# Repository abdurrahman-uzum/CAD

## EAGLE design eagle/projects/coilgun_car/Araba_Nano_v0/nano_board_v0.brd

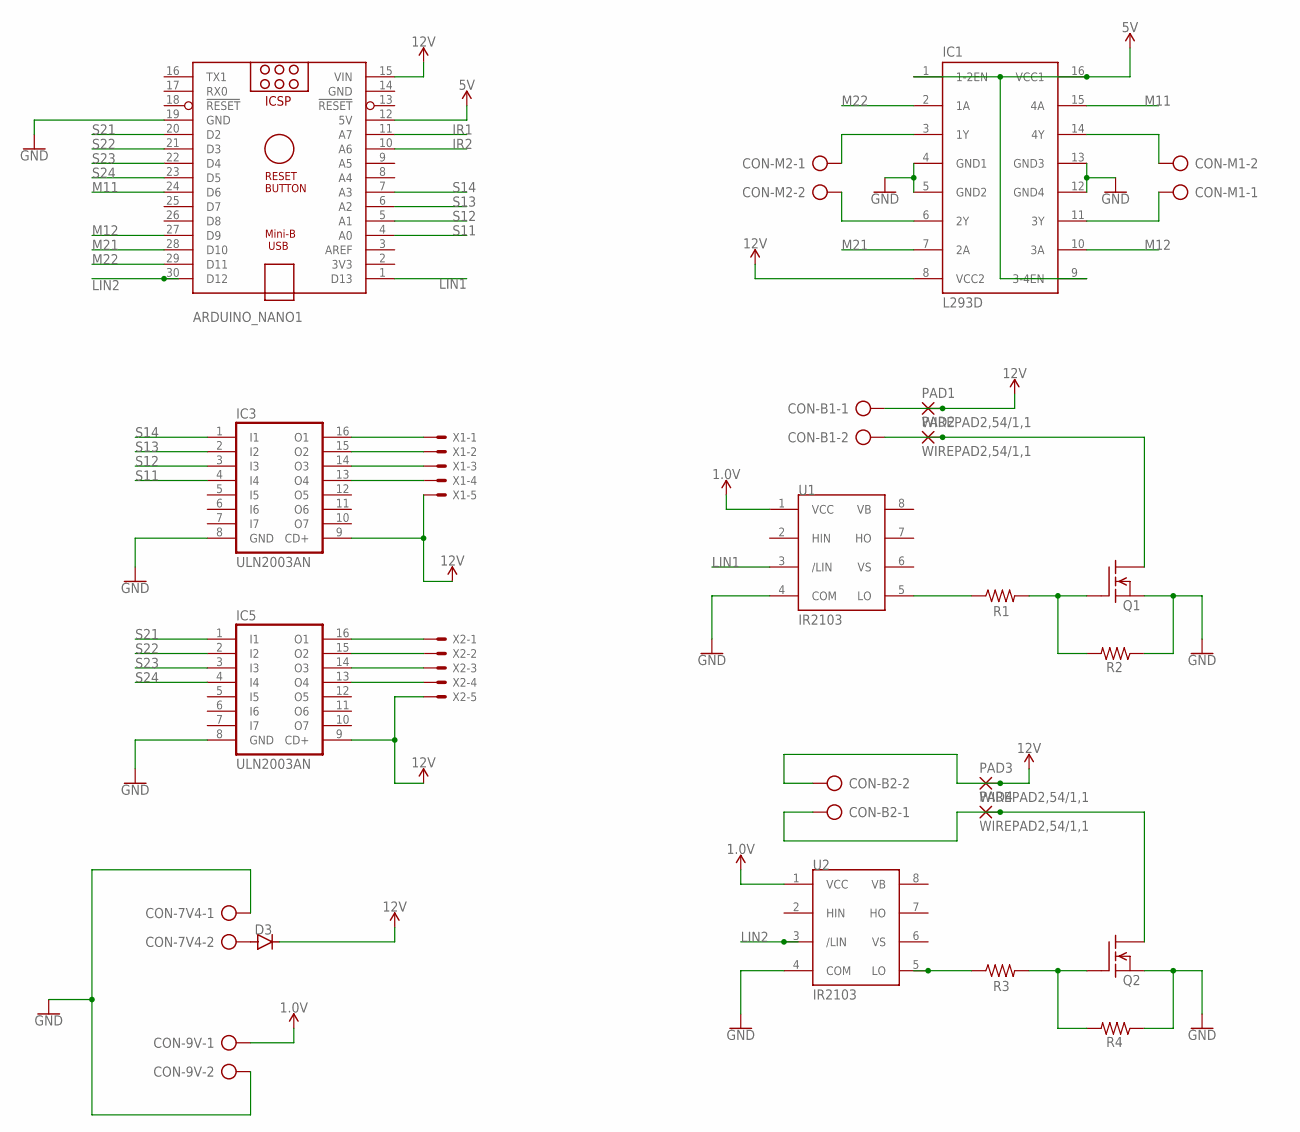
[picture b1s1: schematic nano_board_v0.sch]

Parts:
ARDUINO_NANO1: ARDUINO_NANO
CON-7V4, CON-9V: AK500/2
CON-B1, CON-B2: AK500/2
CON-M1, CON-M2: AK500/2
D3: 1N4004; DO41-10
IC1: L293D; DIL16
IC3, IC5: ULN2003AN; DIL16
PAD1, PAD2, PAD3, PAD4: WIREPAD2,54/1,1; 2,54/1,1
Q1, Q2: IRF510; TO220
R1, R2, R3, R4: R-US_0204/7; 0204/7
U1, U2: IR2103; DIL08
X1, X2: JST-XH-05-PIN-LONG-PAD; JST-XH-05-PACKAGE-LONG-PAD

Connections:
1.0V: CON-9V.1, U1.1 (VCC), U2.1 (VCC)
5V: ARDUINO_NANO1.12 (5V), IC1.1 (1-2EN), IC1.9 (3-4EN), IC1.16 (VCC1)
12V: ARDUINO_NANO1.15 (VIN), CON-B1.1, CON-B2.2, D3.C, IC1.8 (VCC2), IC3.9 (CD+), IC5.9 (CD+), PAD1.1, PAD3.1, X1.5, X2.5
GND: ARDUINO_NANO1.14 (GND), ARDUINO_NANO1.19 (GND), CON-7V4.1, CON-9V.2, IC1.4 (GND1), IC1.5 (GND2), IC1.12 (GND4), IC1.13 (GND3), IC3.8 (GND), IC5.8 (GND), Q1.3 (S), Q2.3 (S), R2.1, R4.1, U1.4 (COM), U2.4 (COM)
IR1: ARDUINO_NANO1.11 (A7)
IR2: ARDUINO_NANO1.10 (A6)
LIN1: ARDUINO_NANO1.1 (D13), U1.3 (/LIN)
LIN2: ARDUINO_NANO1.30 (D12), U2.3 (/LIN)
M11: ARDUINO_NANO1.24 (D6), IC1.15 (4A)
M12: ARDUINO_NANO1.27 (D9), IC1.10 (3A)
M21: ARDUINO_NANO1.28 (D10), IC1.7 (2A)
M22: ARDUINO_NANO1.29 (D11), IC1.2 (1A)
unnamed: R1.1, U1.5 (LO)
unnamed: Q1.1 (G), R1.2, R2.2
unnamed: R3.1, U2.5 (LO)
unnamed: IC3.16 (O1), X1.1
unnamed: IC3.15 (O2), X1.2
unnamed: CON-M1.2, IC1.14 (4Y)
unnamed: CON-M1.1, IC1.11 (3Y)
unnamed: CON-M2.1, IC1.3 (1Y)
unnamed: CON-M2.2, IC1.6 (2Y)
unnamed: CON-B1.2, PAD2.1, Q1.2 (D)
unnamed: Q2.1 (G), R3.2, R4.2
unnamed: IC3.14 (O3), X1.3
unnamed: IC3.13 (O4), X1.4
unnamed: IC5.16 (O1), X2.1
unnamed: IC5.15 (O2), X2.2
unnamed: CON-B2.1, PAD4.1, Q2.2 (D)
unnamed: CON-7V4.2, D3.A
unnamed: IC5.14 (O3), X2.3
unnamed: IC5.13 (O4), X2.4
S11: ARDUINO_NANO1.4 (A0), IC3.4 (I4)
S12: ARDUINO_NANO1.5 (A1), IC3.3 (I3)
S13: ARDUINO_NANO1.6 (A2), IC3.2 (I2)
S14: ARDUINO_NANO1.7 (A3), IC3.1 (I1)
S21: ARDUINO_NANO1.20 (D2), IC5.1 (I1)
S22: ARDUINO_NANO1.21 (D3), IC5.2 (I2)
S23: ARDUINO_NANO1.22 (D4), IC5.3 (I3)
S24: ARDUINO_NANO1.23 (D5), IC5.4 (I4)

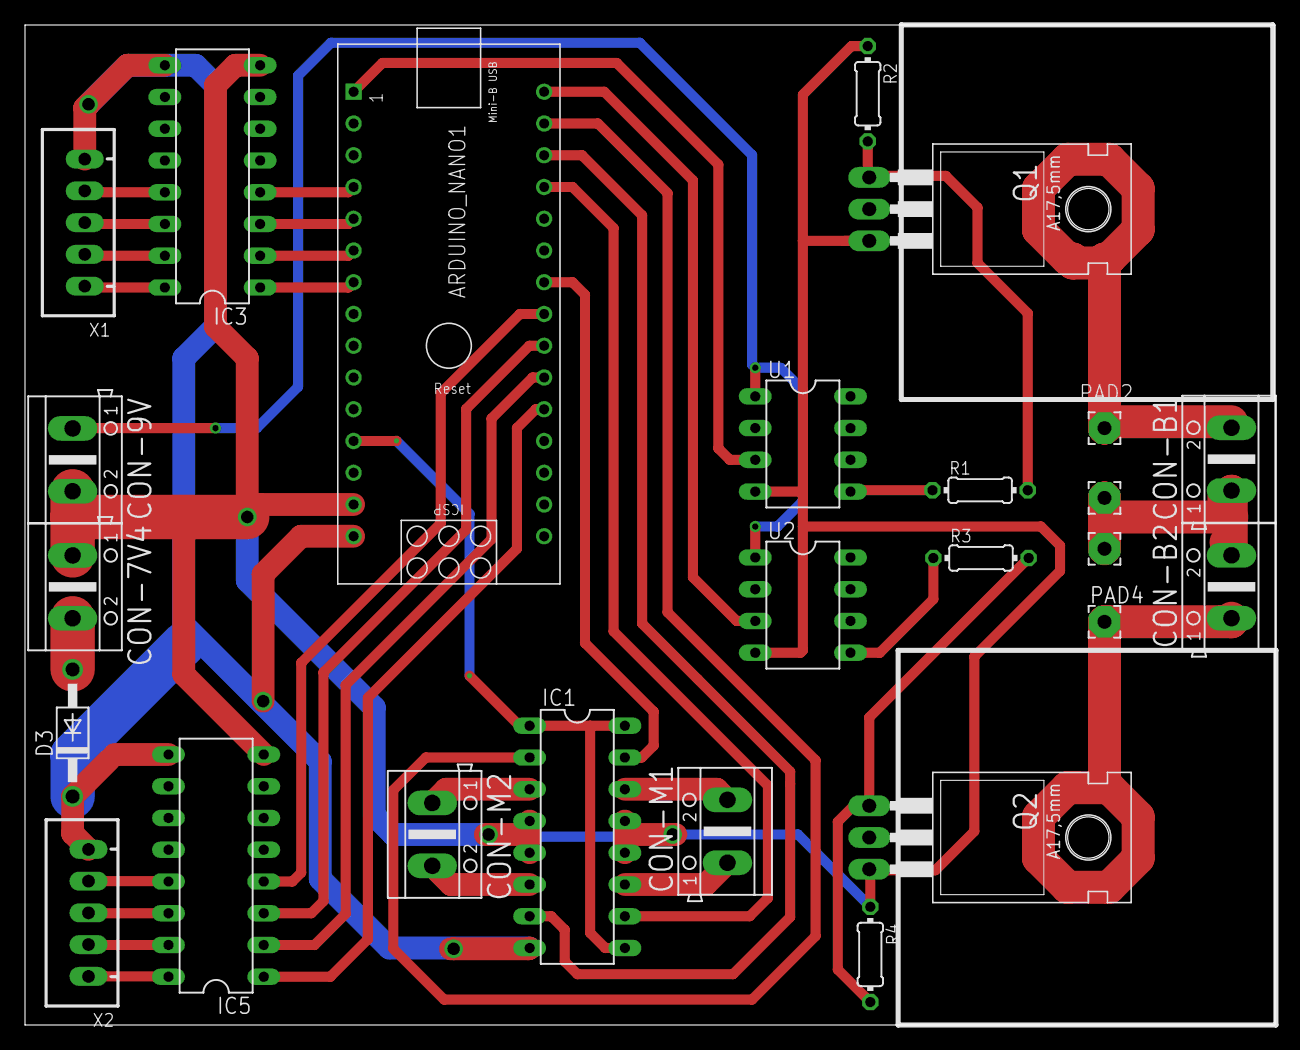
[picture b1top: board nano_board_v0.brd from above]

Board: 2 copper layers, 100.0 x 80.0 mm, 25 parts (0 on the bottom side), 37 nets.

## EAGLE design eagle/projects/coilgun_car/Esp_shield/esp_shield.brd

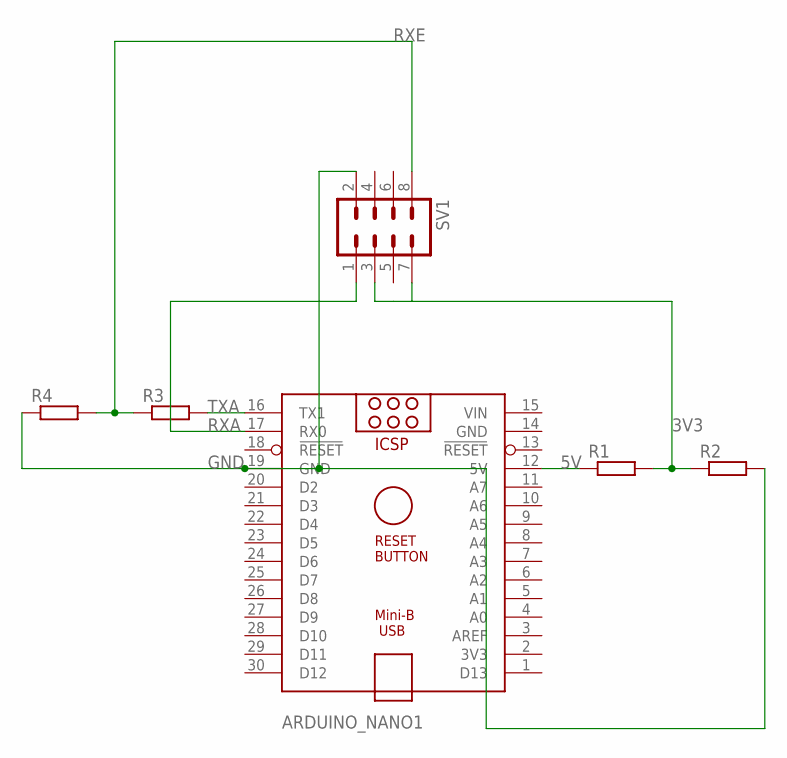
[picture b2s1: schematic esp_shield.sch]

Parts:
ARDUINO_NANO1: ARDUINO_NANO
R1, R2, R3, R4: R-EU_0204/7; 0204/7
SV1: MA04-2

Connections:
3V3: R1.2, R2.1, SV1.3, SV1.7
5V: ARDUINO_NANO1.12 (5V), R1.1
GND: ARDUINO_NANO1.14 (GND), ARDUINO_NANO1.19 (GND), R2.2, R4.1, SV1.2
RXA: ARDUINO_NANO1.17 (RX0), SV1.1
RXE: R3.1, R4.2, SV1.8
TXA: ARDUINO_NANO1.16 (TX1), R3.2
VIN: ARDUINO_NANO1.15 (VIN)

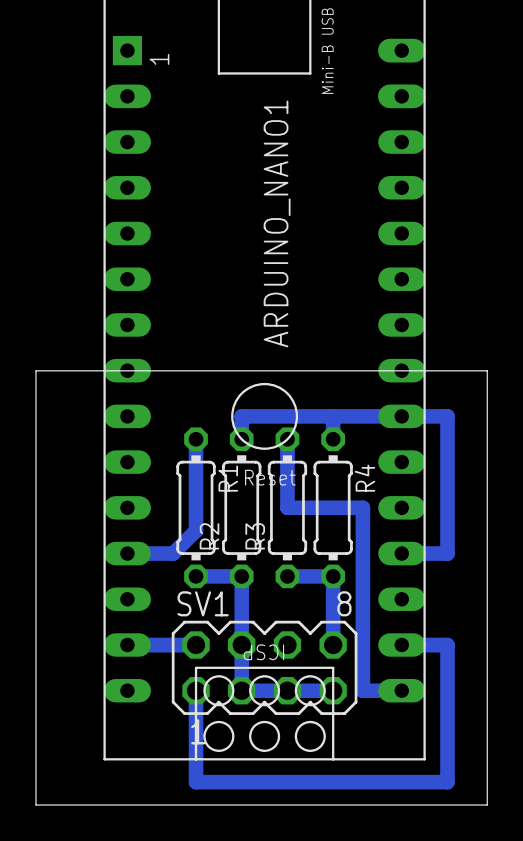
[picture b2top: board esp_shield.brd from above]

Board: 2 copper layers, 25.1 x 24.1 mm, 6 parts (0 on the bottom side), 6 nets.

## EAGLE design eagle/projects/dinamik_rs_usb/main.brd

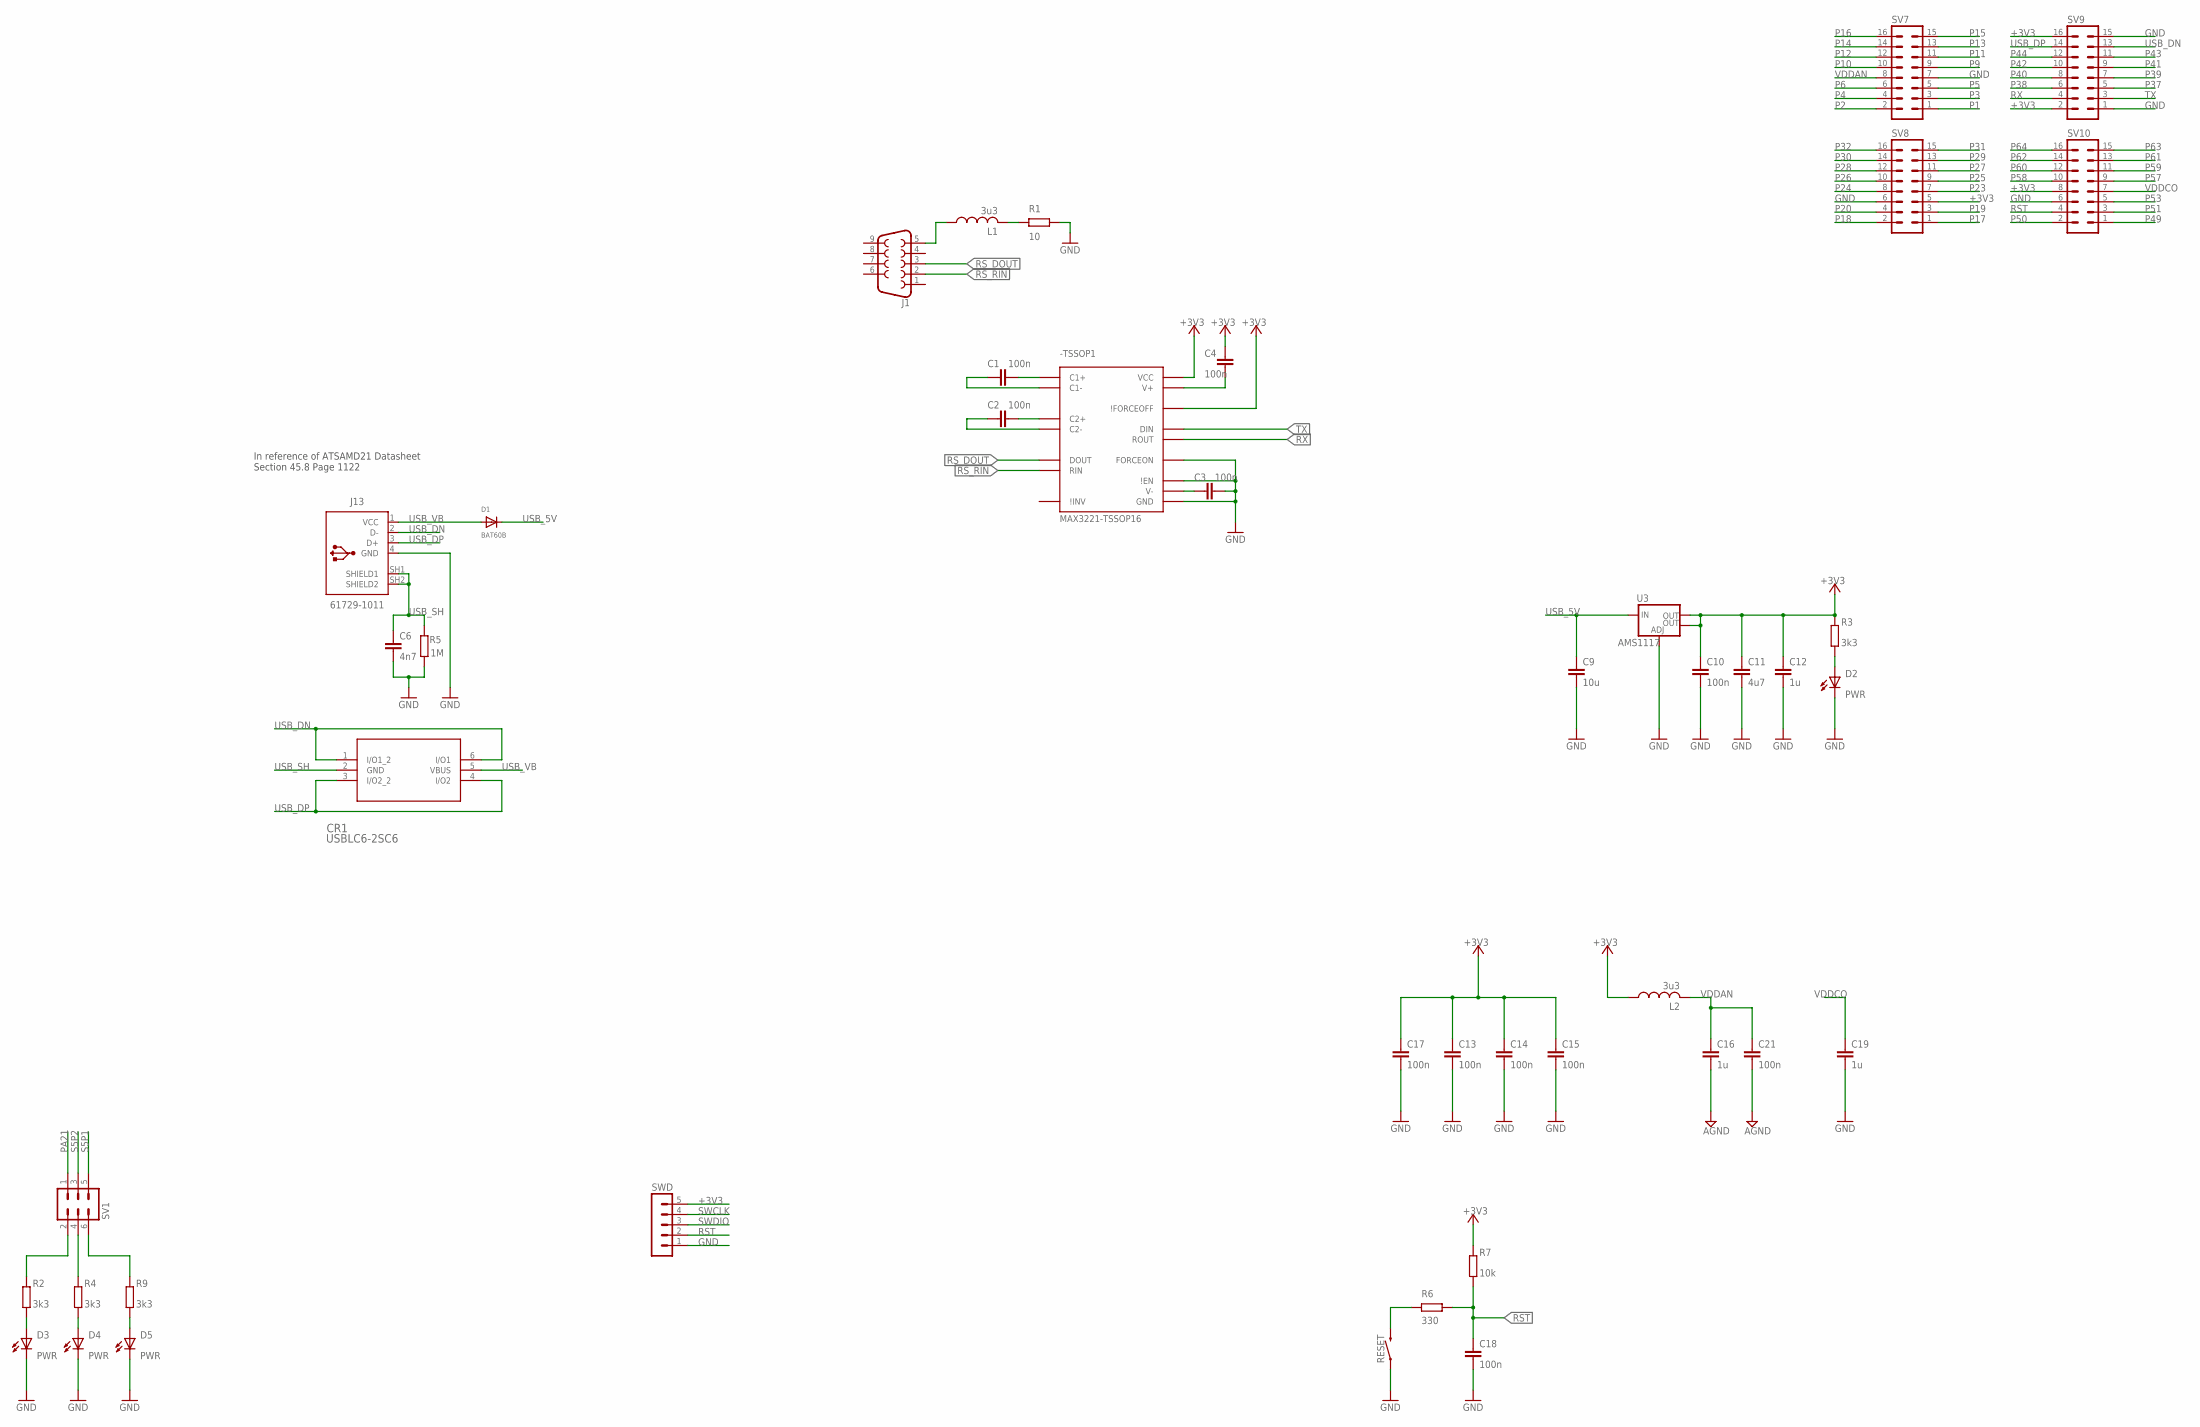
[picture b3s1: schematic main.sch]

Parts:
-TSSOP1: MAX3221-TSSOP16; TSSOP16
C1, C2, C3, C4, C10, C13, C14, C15, C17, C18, C21: 100n; C0603
C6: 4n7; C0603
C9: 10u; C0603
C11: 4u7; C0603
C12, C16, C19: 1u; C0603
CR1: USBLC6-2SC6; SOT23-6L_STM
D1: BAT60B; SOD-323F
D2, D3, D4, D5: PWR; CHIPLED_0805
J1: DB9FEMALE; DB9
J13: 61729-1011; 61729-1011BLF
L1, L2: 3u3; L3216C
R1: 10; R0603
R2, R3, R4, R9: 3k3; R0603
R5: 1M; R0603
R6: 330; R0603
R7: 10k; R0603
RESET: MOMENTARY-SWITCH-SPST-SMD-6.0X3.5MM; TACTILE_SWITCH_SMD_6.0X3.5MM
SV1: MA03-2
SV7, SV8, SV9, SV10: MA08-2
SWD: MA05-1
U3: AMS1117; SOT223

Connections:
+3V3: -TSSOP1.15 (VCC), -TSSOP1.16 (\!FORCEOFF), C4.2, C10.1, C11.1, C12.1, C13.1, C14.1, C15.1, C17.1, L2.1, R3.2, R7.1, SV8.5, SV9.2, SV9.16, SV10.8, SWD.5, U3.2 (OUT), U3.4 (OUT)
GND: -TSSOP1.1 (\!EN), -TSSOP1.12 (FORCEON), -TSSOP1.14 (GND), C3.2, C6.2, C9.2, C10.2, C11.2, C12.2, C13.2, C14.2, C15.2, C16.2, C17.2, C18.2, C19.2, C21.2, D2.C, D3.C, D4.C, D5.C, J13.4 (GND), R1.2, R5.2, RESET.1, SV7.7, SV8.6, SV9.1, SV9.15, SV10.6, SWD.1, U3.1 (ADJ)
unnamed: -TSSOP1.4 (C1-), C1.1
unnamed: R6.1, RESET.2
unnamed: -TSSOP1.7 (V-), C3.1
unnamed: D2.A, R3.1
unnamed: D3.A, R2.1
unnamed: D4.A, R4.1
unnamed: -TSSOP1.6 (C2-), C2.1
unnamed: J1.5, L1.1
unnamed: D5.A, R9.1
unnamed: R2.2, SV1.2
unnamed: R4.2, SV1.4
unnamed: R9.2, SV1.6
unnamed: -TSSOP1.3 (V+), C4.1
unnamed: L1.2, R1.1
unnamed: -TSSOP1.2 (C1+), C1.2
unnamed: -TSSOP1.5 (C2+), C2.2
P1: SV7.1
P2: SV7.2
P3: SV7.3
P4: SV7.4
P5: SV7.5
P6: SV7.6
P9: SV7.9
P10: SV7.10
P11: SV7.11
P12: SV7.12
P13: SV7.13
P14: SV7.14
P15: SV7.15
P16: SV7.16
P17: SV8.1
P18: SV8.2
P19: SV8.3
P20: SV8.4
P23: SV8.7
P24: SV8.8
P25: SV8.9
P26: SV8.10
P27: SV8.11
P28: SV8.12
P29: SV8.13
P30: SV8.14
P31: SV8.15
P32: SV8.16
P37: SV9.5
P38: SV9.6
P39: SV9.7
P40: SV9.8
P41: SV9.9
P42: SV9.10
P43: SV9.11
P44: SV9.12
P49: SV10.1
P50: SV10.2
P51: SV10.3
P53: SV10.5
P57: SV10.9
P58: SV10.10
P59: SV10.11
P60: SV10.12
P61: SV10.13
P62: SV10.14
P63: SV10.15
P64: SV10.16
PA21: SV1.1
RST: C18.1, R6.2, R7.2, SV10.4, SWD.2
RS_DOUT: -TSSOP1.13 (DOUT), J1.3
RS_RIN: -TSSOP1.8 (RIN), J1.2
RX: -TSSOP1.9 (ROUT), SV9.4
S5P1: SV1.5
S5P2: SV1.3
SWCLK: SWD.4
SWDIO: SWD.3
TX: -TSSOP1.11 (DIN), SV9.3
USB_5V: C9.1, D1.C, U3.3 (IN)
USB_DN: CR1.1 (I/O1_2), CR1.6 (I/O1), J13.2 (D-), SV9.13
USB_DP: CR1.3 (I/O2_2), CR1.4 (I/O2), J13.3 (D+), SV9.14
USB_SH: C6.1, CR1.2 (GND), J13.SH1 (SHIELD1), J13.SH2 (SHIELD2), R5.1
USB_VB: CR1.5 (VBUS), D1.A, J13.1 (VCC)
VDDAN: C16.1, C21.1, L2.2, SV7.8
VDDCO: C19.1, SV10.7

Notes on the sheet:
In reference of ATSAMD21 Datasheet Section 45.8 Page 1122

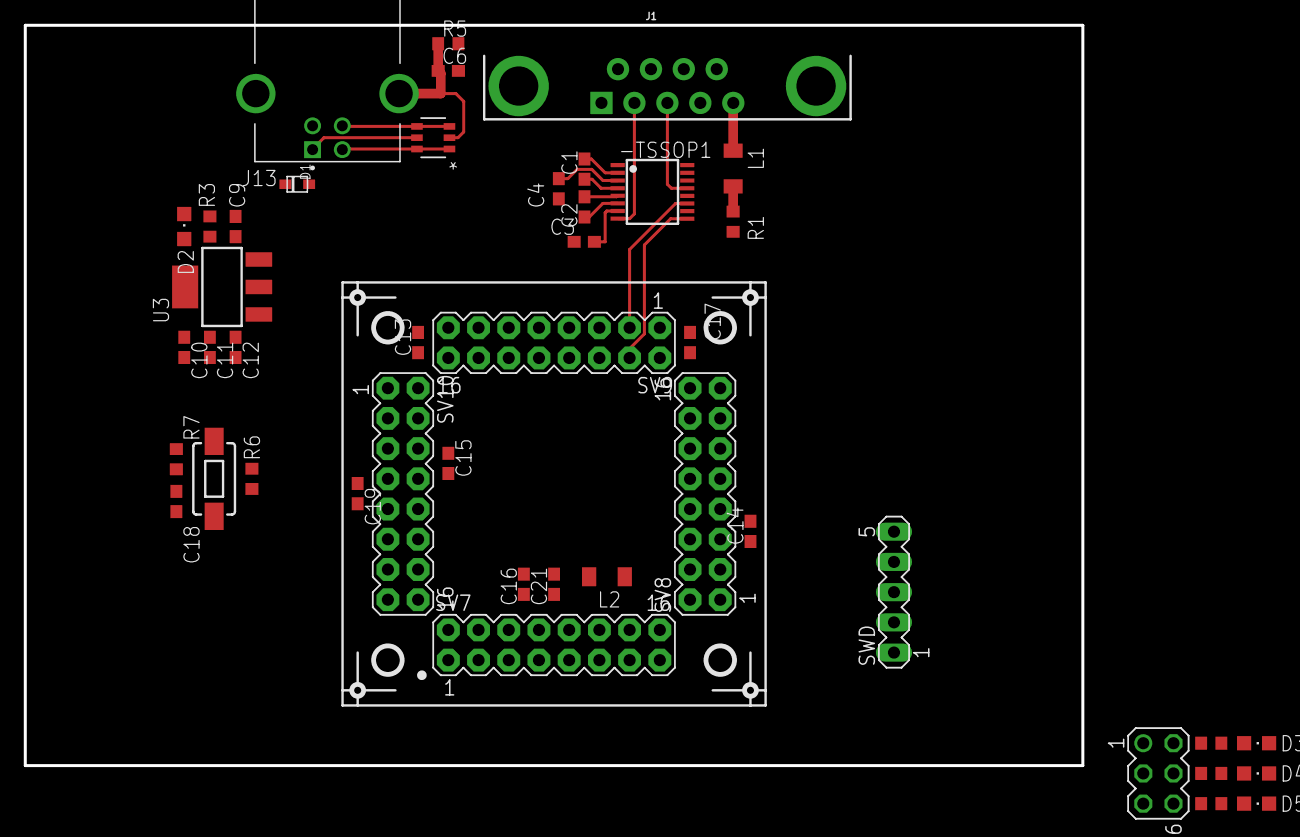
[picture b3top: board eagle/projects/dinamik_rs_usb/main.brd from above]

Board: 2 copper layers, 88.9 x 62.2 mm, 44 parts (0 on the bottom side), 30 nets.

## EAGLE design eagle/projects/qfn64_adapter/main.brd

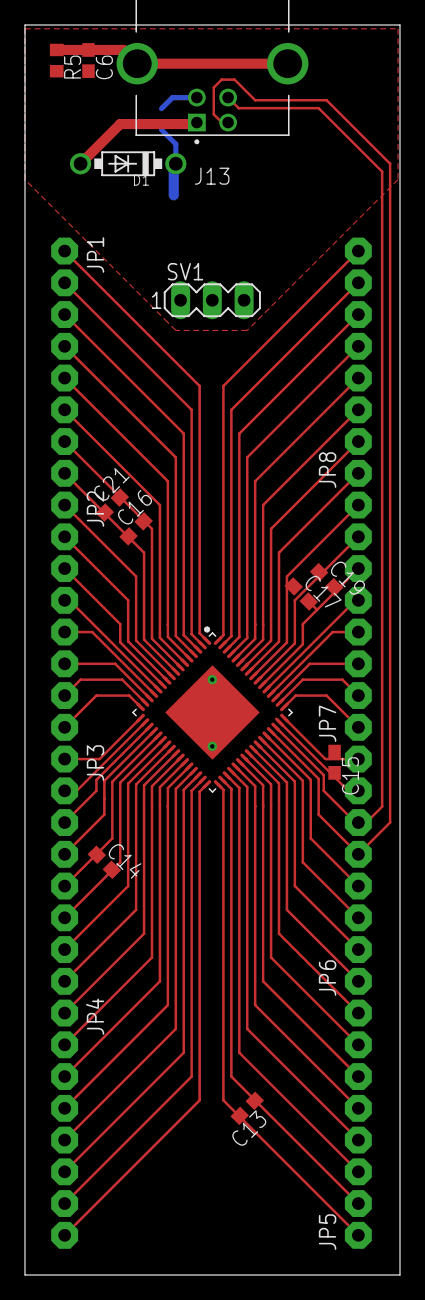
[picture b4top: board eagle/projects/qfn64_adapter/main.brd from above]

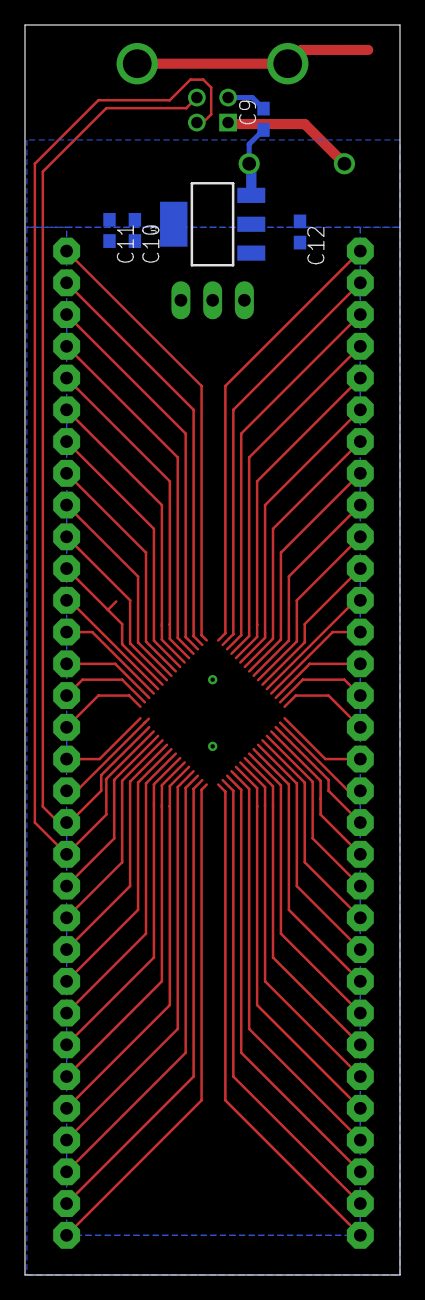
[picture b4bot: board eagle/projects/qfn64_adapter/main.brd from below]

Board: 2 copper layers, 30.0 x 100.0 mm, 26 parts (5 on the bottom side), 59 nets.

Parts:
C6: 4n7; C0603
C9: 10u; C0603
C10, C13, C14, C15, C17, C21: 100n; C0603
C11: 4u7; C0603
C12, C16, C19: 1u; C0603
D1: BAT60B; DO41-7.6
J13: 61729-1011; 61729-1011BLF
JP1, JP2, JP3, JP4, JP5, JP6, JP7, JP8: 1X08-CLEANBIG
R5: 1M; R0603
SV1: MA03-1
U3: AMS1117; SOT223
U$1: QFN50P900X900X100-65T535

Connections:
+3V3: C10.1, C11.1, C12.1, C13.1, C14.1, C15.1, C16.1, C17.1, C21.1, JP1.8, JP3.5, JP5.2, JP6.8, JP7.8, U3.2, U3.4, U$1.8, U$1.21, U$1.34, U$1.48, U$1.56
GND: C6.2, C9.2, C10.2, C11.2, C12.2, C13.2, C14.2, C15.2, C16.2, C17.2, C19.2, C21.2, J13.4, JP1.7, JP3.6, JP5.1, JP6.7, JP7.6, R5.2, SV1.1, SV1.2, SV1.3, U3.1, U$1.7, U$1.22, U$1.33, U$1.47, U$1.54, U$1.65
P1: JP1.1, U$1.1
P2: JP1.2, U$1.2
P3: JP1.3, U$1.3
P4: JP1.4, U$1.4
P5: JP1.5, U$1.5
P6: JP1.6, U$1.6
P9: JP2.1, U$1.9
P10: JP2.2, U$1.10
P11: JP2.3, U$1.11
P12: JP2.4, U$1.12
P13: JP2.5, U$1.13
P14: JP2.6, U$1.14
P15: JP2.7, U$1.15
P16: JP2.8, U$1.16
P17: JP3.1, U$1.17
P18: JP3.2, U$1.18
P19: JP3.3, U$1.19
P20: JP3.4, U$1.20
P23: JP3.7, U$1.23
P24: JP3.8, U$1.24
P25: JP4.1, U$1.25
P26: JP4.2, U$1.26
P27: JP4.3, U$1.27
P28: JP4.4, U$1.28
P29: JP4.5, U$1.29
P30: JP4.6, U$1.30
P31: JP4.7, U$1.31
P32: JP4.8, U$1.32
P35: JP5.3, U$1.35
P36: JP5.4, U$1.36
P37: JP5.5, U$1.37
P38: JP5.6, U$1.38
P39: JP5.7, U$1.39
P40: JP5.8, U$1.40
P41: JP6.1, U$1.41
P42: JP6.2, U$1.42
P43: JP6.3, U$1.43
P44: JP6.4, U$1.44
P49: JP7.1, U$1.49
P50: JP7.2, U$1.50
P51: JP7.3, U$1.51
P52: JP7.4, U$1.52
P53: JP7.5, U$1.53
P57: JP8.1, U$1.57
P58: JP8.2, U$1.58
P59: JP8.3, U$1.59
P60: JP8.4, U$1.60
P61: JP8.5, U$1.61
P62: JP8.6, U$1.62
P63: JP8.7, U$1.63
P64: JP8.8, U$1.64
USB_5V: C9.1, D1.C, U3.3
USB_DN: J13.2, JP6.5, U$1.45
USB_DP: J13.3, JP6.6, U$1.46
USB_SH: C6.1, J13.SH1, J13.SH2, R5.1
USB_VB: D1.A, J13.1
VDDCO: C19.1, JP7.7, U$1.55

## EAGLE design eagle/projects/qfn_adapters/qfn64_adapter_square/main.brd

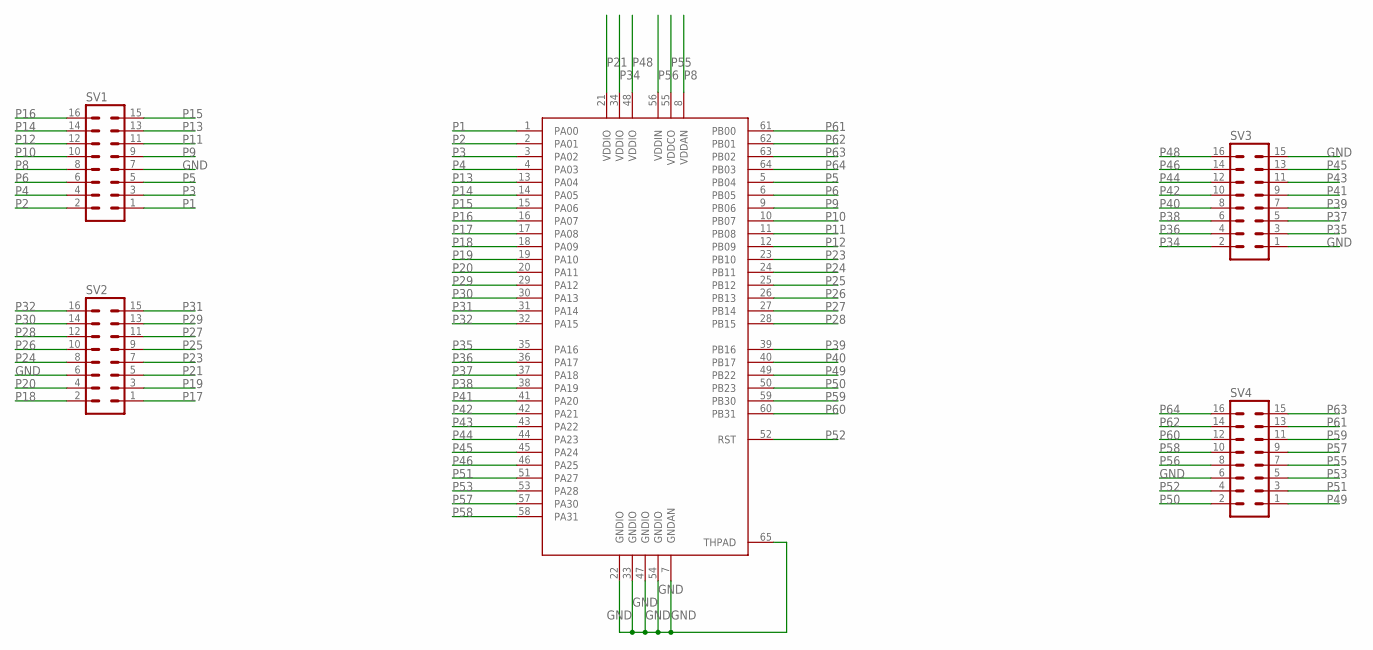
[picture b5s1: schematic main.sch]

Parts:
SV1, SV2, SV3, SV4: MA08-2
U$1: ATSAMD21J18AQFN64; QFN50P900X900X100-65T535

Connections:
GND: SV1.7, SV2.6, SV3.1, SV3.15, SV4.6, U$1.7 (GNDAN), U$1.22 (GNDIO), U$1.33 (GNDIO), U$1.47 (GNDIO), U$1.54 (GNDIO), U$1.65 (THPAD)
P1: SV1.1, U$1.1 (PA00)
P2: SV1.2, U$1.2 (PA01)
P3: SV1.3, U$1.3 (PA02)
P4: SV1.4, U$1.4 (PA03)
P5: SV1.5, U$1.5 (PB04)
P6: SV1.6, U$1.6 (PB05)
P8: SV1.8, U$1.8 (VDDAN)
P9: SV1.9, U$1.9 (PB06)
P10: SV1.10, U$1.10 (PB07)
P11: SV1.11, U$1.11 (PB08)
P12: SV1.12, U$1.12 (PB09)
P13: SV1.13, U$1.13 (PA04)
P14: SV1.14, U$1.14 (PA05)
P15: SV1.15, U$1.15 (PA06)
P16: SV1.16, U$1.16 (PA07)
P17: SV2.1, U$1.17 (PA08)
P18: SV2.2, U$1.18 (PA09)
P19: SV2.3, U$1.19 (PA10)
P20: SV2.4, U$1.20 (PA11)
P21: SV2.5, U$1.21 (VDDIO)
P23: SV2.7, U$1.23 (PB10)
P24: SV2.8, U$1.24 (PB11)
P25: SV2.9, U$1.25 (PB12)
P26: SV2.10, U$1.26 (PB13)
P27: SV2.11, U$1.27 (PB14)
P28: SV2.12, U$1.28 (PB15)
P29: SV2.13, U$1.29 (PA12)
P30: SV2.14, U$1.30 (PA13)
P31: SV2.15, U$1.31 (PA14)
P32: SV2.16, U$1.32 (PA15)
P34: SV3.2, U$1.34 (VDDIO)
P35: SV3.3, U$1.35 (PA16)
P36: SV3.4, U$1.36 (PA17)
P37: SV3.5, U$1.37 (PA18)
P38: SV3.6, U$1.38 (PA19)
P39: SV3.7, U$1.39 (PB16)
P40: SV3.8, U$1.40 (PB17)
P41: SV3.9, U$1.41 (PA20)
P42: SV3.10, U$1.42 (PA21)
P43: SV3.11, U$1.43 (PA22)
P44: SV3.12, U$1.44 (PA23)
P45: SV3.13, U$1.45 (PA24)
P46: SV3.14, U$1.46 (PA25)
P48: SV3.16, U$1.48 (VDDIO)
P49: SV4.1, U$1.49 (PB22)
P50: SV4.2, U$1.50 (PB23)
P51: SV4.3, U$1.51 (PA27)
P52: SV4.4, U$1.52 (RST)
P53: SV4.5, U$1.53 (PA28)
P55: SV4.7, U$1.55 (VDDCO)
P56: SV4.8, U$1.56 (VDDIN)
P57: SV4.9, U$1.57 (PA30)
P58: SV4.10, U$1.58 (PA31)
P59: SV4.11, U$1.59 (PB30)
P60: SV4.12, U$1.60 (PB31)
P61: SV4.13, U$1.61 (PB00)
P62: SV4.14, U$1.62 (PB01)
P63: SV4.15, U$1.63 (PB02)
P64: SV4.16, U$1.64 (PB03)

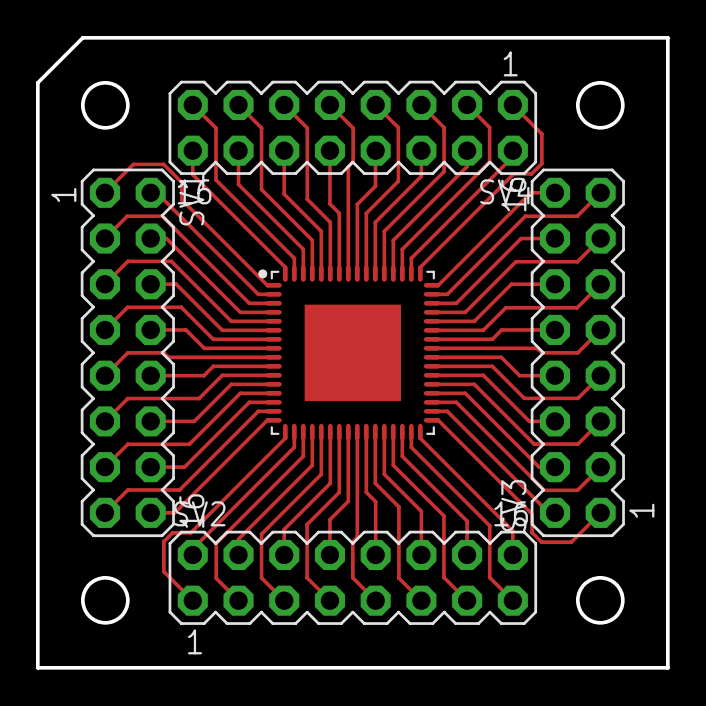
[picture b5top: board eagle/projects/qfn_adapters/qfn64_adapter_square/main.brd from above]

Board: 2 copper layers, 35.0 x 35.0 mm, 5 parts (0 on the bottom side), 60 nets.

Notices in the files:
parts and their libraries:
SparkFun-PowerSymbols: Licensing: Creative Commons ShareAlike 4.0 International - https://creativecommons.org/licenses/by-sa/4.0
COPYRIGHT: Copyright (C) 2023 Ultra Librarian. All rights reserved.
